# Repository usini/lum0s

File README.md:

# lum0s
 
a LED strip powered by a USB power bank   
Based on https://github.com/FabLab-Luenen/McLighting

Tested Features (see McLighting repo for more information):
* Lots of animations
* Websockets control
* Web interface (sadly not really useable with phone as of now)
* E1.31 (DMX512 over WiFi) : http://www.live-leds.de/
* Retain last state
* Button Control (for now only one)
* IR Remote support
* MQTT Support

Planned features (these features will be posted on FabLab-Luenen repo)
* Microphone
* 3 buttons controls (Maybe 2 buttons to control light and 1 for choosing to enable/disable WiFi)
* PIR support
* I2C Sensors (still not a clear idea of which to use)
* SSDP / Netbios support
* Password (as for now it is unprotected)

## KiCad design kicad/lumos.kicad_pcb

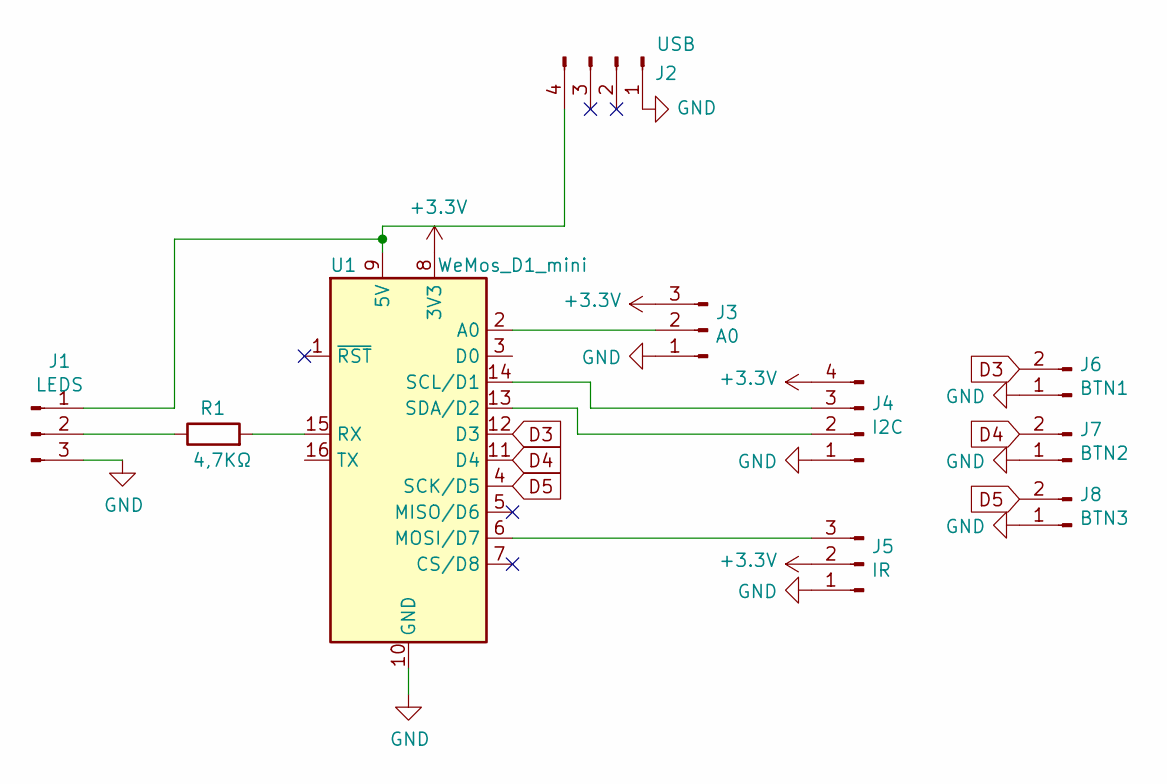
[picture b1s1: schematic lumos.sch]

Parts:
J1: LEDS; ws282b
J2: USB; PinHeader_1x04_P2.54mm_Vertical
J3: A0; PinHeader_1x03_P2.54mm_Vertical
J4: I2C; PinHeader_1x04_P2.54mm_Vertical
J5: IR; PinHeader_1x03_P2.54mm_Vertical
J6: BTN1; PinHeader_1x02_P2.54mm_Vertical
J7: BTN2; PinHeader_1x02_P2.54mm_Vertical
J8: BTN3; PinHeader_1x02_P2.54mm_Vertical
R1: 4,7KΩ; R_Axial_DIN0309_L9.0mm_D3.2mm_P12.70mm_Horizontal
U1: WeMos_D1_mini; WEMOS_D1_mini_light

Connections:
+3V3: J3.3, J4.4, J5.2, U1.8 (3V3)
D3: J6.2, U1.12 (D3)
D4: J7.2, U1.11 (D4)
D5: J8.2, U1.4 (SCK/D5)
GND: J1.3, J2.1, J3.1, J4.1, J5.1, J6.1, J7.1, J8.1, U1.10 (GND)
unnamed: J1.1, J2.4, U1.9 (5V)
unnamed: J1.2, R1.1
unnamed: J3.2, U1.2 (A0)
unnamed: J4.2, U1.13 (SDA/D2)
unnamed: J4.3, U1.14 (SCL/D1)
unnamed: J5.3, U1.6 (MOSI/D7)
unnamed: R1.2, U1.15 (RX)

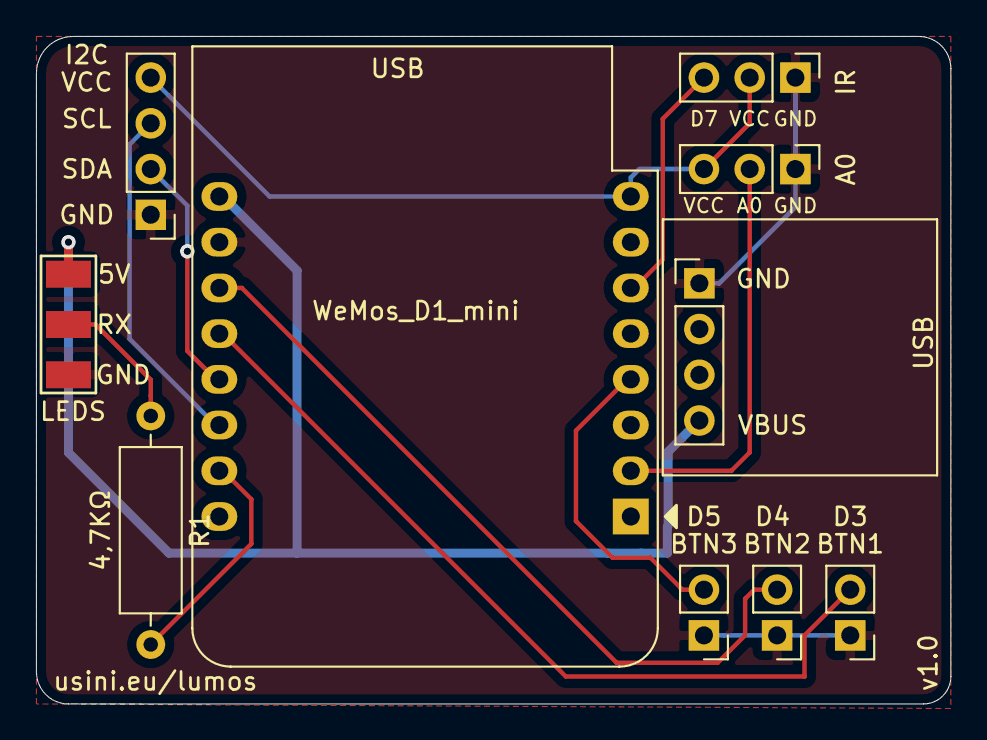
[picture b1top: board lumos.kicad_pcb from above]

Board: 2 copper layers, 50.8 x 37.1 mm, 10 parts (0 on the bottom side), 12 nets.

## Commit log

2020-01-29 Readme/image correction
2020-01-29 Create LICENSE
